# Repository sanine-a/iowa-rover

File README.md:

iowa-rover
==========

hardware & software for the new Iowa Mars rover exhibit.

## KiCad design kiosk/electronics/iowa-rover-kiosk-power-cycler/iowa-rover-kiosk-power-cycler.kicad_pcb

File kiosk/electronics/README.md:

Iowa Science Rover - Electronics
================================

Due to the myriad inputs and outputs that need to be managed, the electronics of the kiosk have been split into
a constellation of connected boards rather than using a single monolithic board. The scheme of connections is
as follows:

[

  * **Arduino Mega**: This is an ATmega2560-based microcontroller, used as the central processor for the kiosk.
  * **Mega Adapter**: This provides a convenient 40-pin ribbon cable connection between the Arduino Mega and the
    main board. It carries power from the main board to the Arduino.
  * **Main Board**: The heart of the kiosk. It carries the comms radio, the 5V regulator to step down from the 12V
    power supply, the ATtiny84 chip to drive the RFID programmer's RFID reader, and connectors to attach all of the
    peripheral boards to the Arduino.
  * **RFID Programmer**: This board carries an ID-12LA RFID reader and a set of buttons. It is used to configure new
    tags appropriately so that they will work with the kiosk, and it is kept inside the kiosk cabinet under normal
    circumstances. It connects to the main board with a 12-pin ribbon cable.
  * **RFID**: These four identical boards are the RFID readers used to read the tags. They each have their own ID-12LA
    reader and an ATtiny84 chip to drive them over the I2C bus. They also carry jumpers that permit setting the I2C bus
    address of each board, allowing them to be daisy-chained. They connect to each other and to the main board with
    4-pin KK connectors.
  * **Lamps**: This board drives the lamps above the RFID readers, the READY, ERROR, and RUNNING lamps, and both the
    lamp and button inside the TRANSMIT button. It is connected to the main board with an 8-pin ribbon cable.
  * **Level Buttons**: This board drives the lamps and buttons below the RFID readers (but not the bar graphs). It is
    connnected to the main board with a 16-pin ribbon cable.
  * **LEDs**: These NeoPixels are the bar graphs, and are chained together with wire-to-wire inline connectors. They
    connect to the main board with a 3-pin KK connector.

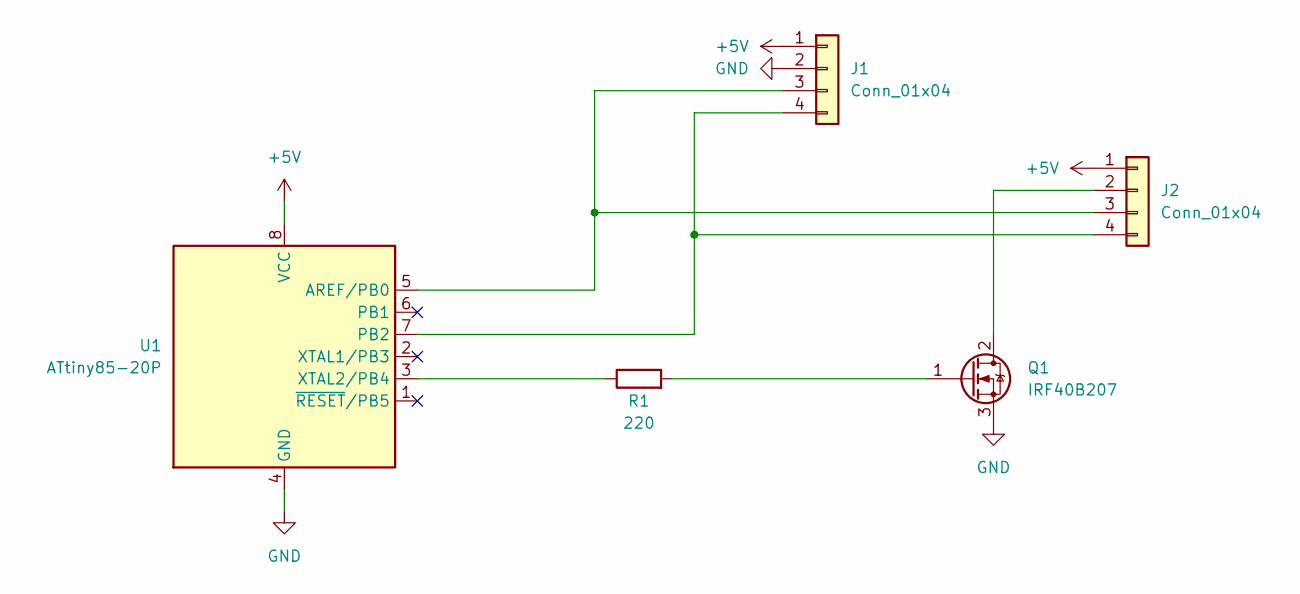
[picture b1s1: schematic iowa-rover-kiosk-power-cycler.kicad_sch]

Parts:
J1, J2: Conn_01x04; Molex_KK-254_AE-6410-04A_1x04_P2.54mm_Vertical
Q1: IRF40B207; TO-220-3_Vertical
R1: 220; R_Axial_DIN0207_L6.3mm_D2.5mm_P7.62mm_Horizontal
U1: ATtiny85-20P; DIP-8_W7.62mm

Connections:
+5V: J1.1, J2.1, U1.8 (VCC)
GND: J1.2, Q1.3 (S), U1.4 (GND)
unnamed: J1.3, J2.3, U1.5 (AREF/PB0)
unnamed: J1.4, J2.4, U1.7 (PB2)
unnamed: J2.2, Q1.2 (D)
unnamed: Q1.1 (G), R1.2
unnamed: R1.1, U1.3 (XTAL2/PB4)

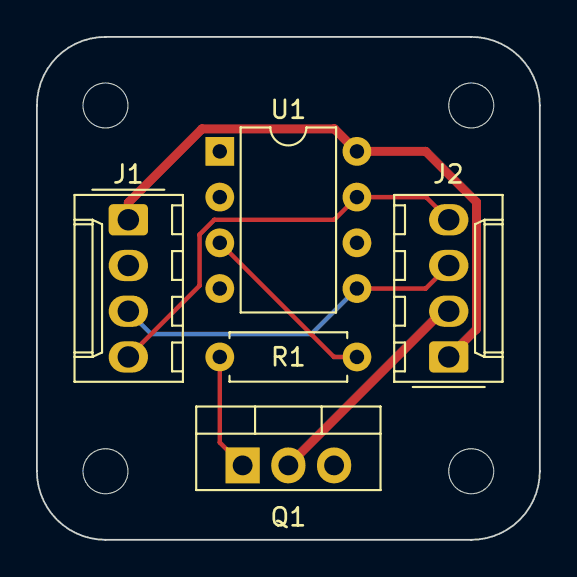
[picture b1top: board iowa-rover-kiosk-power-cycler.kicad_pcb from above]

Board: 2 copper layers, 27.9 x 27.9 mm, 5 parts (0 on the bottom side), 7 nets.

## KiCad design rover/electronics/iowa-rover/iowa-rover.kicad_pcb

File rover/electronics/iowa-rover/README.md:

Iowa Science Rover - Rover Controller
=====================================

The main controller board for the SMM revision of the Iowa Science Rover.

The Metro Mini listens for commands from the kiosk via the radio transceiver, and then executes
the received commands via the motors. The switch allows the controller to choose which kiosk it
listens to, and the trimpot allows maintenance technicians to correct for any directional drift due
to motor wear over time.

Parts
-----

 * [TB6612 Motor Driver](https://www.adafruit.com/product/2448)
 * [RFM69HCW Transceiver](https://www.adafruit.com/product/3070)
 * [Metro Mini v2](https://www.adafruit.com/product/2590)
 * [2k Trimpot](https://www.digikey.com/en/products/detail/bourns-inc/3352T-1-202LF/1088345)
 * [SPDT Switch](https://www.digikey.com/en/products/detail/bourns-inc/3352T-1-202LF/1088345)
 * [USB-C Power Connector](https://www.adafruit.com/product/4907)
 * [Screw Terminals](https://www.digikey.com/en/products/detail/molex/0398800302/2421325)
 * [Motors](https://www.adafruit.com/product/3802)

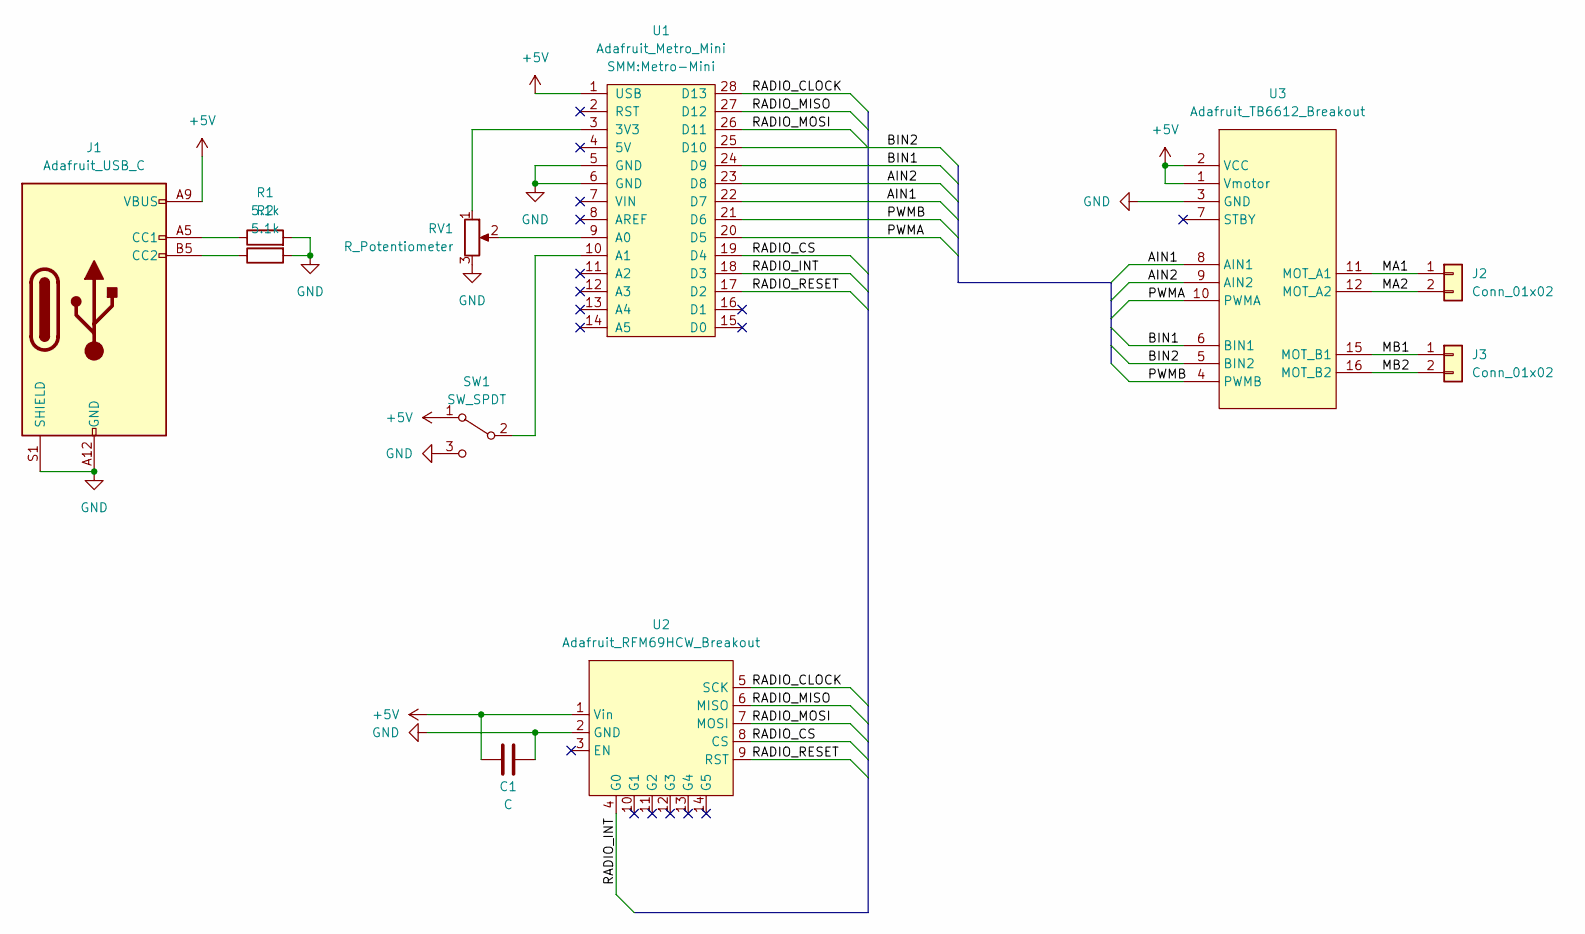
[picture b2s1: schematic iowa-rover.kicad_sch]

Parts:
C1: C; C_Disc_D4.3mm_W1.9mm_P5.00mm
J1: Adafruit_USB_C
J2, J3: Conn_01x02; TerminalBlock-2_P5.08mm_small
R1, R2: 5.1k; Resistor_L6.3mm_D2.5mm_P10.16mm_Horizontal
RV1: R_Potentiometer; Rover_Trimpot
SW1: SW_SPDT; SW_EG1218
U1: Adafruit_Metro_Mini; Metro-Mini
U2: Adafruit_RFM69HCW_Breakout; Adafruit RFM69HCW Breakout
U3: Adafruit_TB6612_Breakout

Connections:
+5V: C1.1, J1.A9 (VBUS), J1.B9 (VBUS), SW1.1 (A), U1.1 (USB), U2.1 (Vin), U3.1 (Vmotor), U3.2 (VCC)
/AIN1: U1.22 (D7), U3.8 (AIN1)
/AIN2: U1.23 (D8), U3.9 (AIN2)
/BIN1: U1.24 (D9), U3.6 (BIN1)
/BIN2: U1.25 (D10), U3.5 (BIN2)
/MA1: J2.1, U3.11 (MOT_A1)
/MA2: J2.2, U3.12 (MOT_A2)
/MB1: J3.1, U3.15 (MOT_B1)
/MB2: J3.2, U3.16 (MOT_B2)
/PWMA: U1.20 (D5), U3.10 (PWMA)
/PWMB: U1.21 (D6), U3.4 (PWMB)
/RADIO_CLOCK: U1.28 (D13), U2.5 (SCK)
/RADIO_CS: U1.19 (D4), U2.8 (CS)
/RADIO_INT: U1.18 (D3), U2.4 (G0)
/RADIO_MISO: U1.27 (D12), U2.6 (MISO)
/RADIO_MOSI: U1.26 (D11), U2.7 (MOSI)
/RADIO_RESET: U1.17 (D2), U2.9 (RST)
GND: C1.2, J1.A12 (GND), J1.B12 (GND), J1.S1 (SHIELD), R1.2, R2.2, RV1.3, SW1.3 (C), U1.5 (GND), U1.6 (GND), U2.2 (GND), U3.3 (GND), U3.13 (GND), U3.14 (GND)
unnamed: J1.A5 (CC1), R1.1
unnamed: J1.B5 (CC2), R2.1
unnamed: SW1.2 (B), U1.10 (A1)
unnamed: RV1.1, U1.3 (3V3)
unnamed: RV1.2, U1.9 (A0)

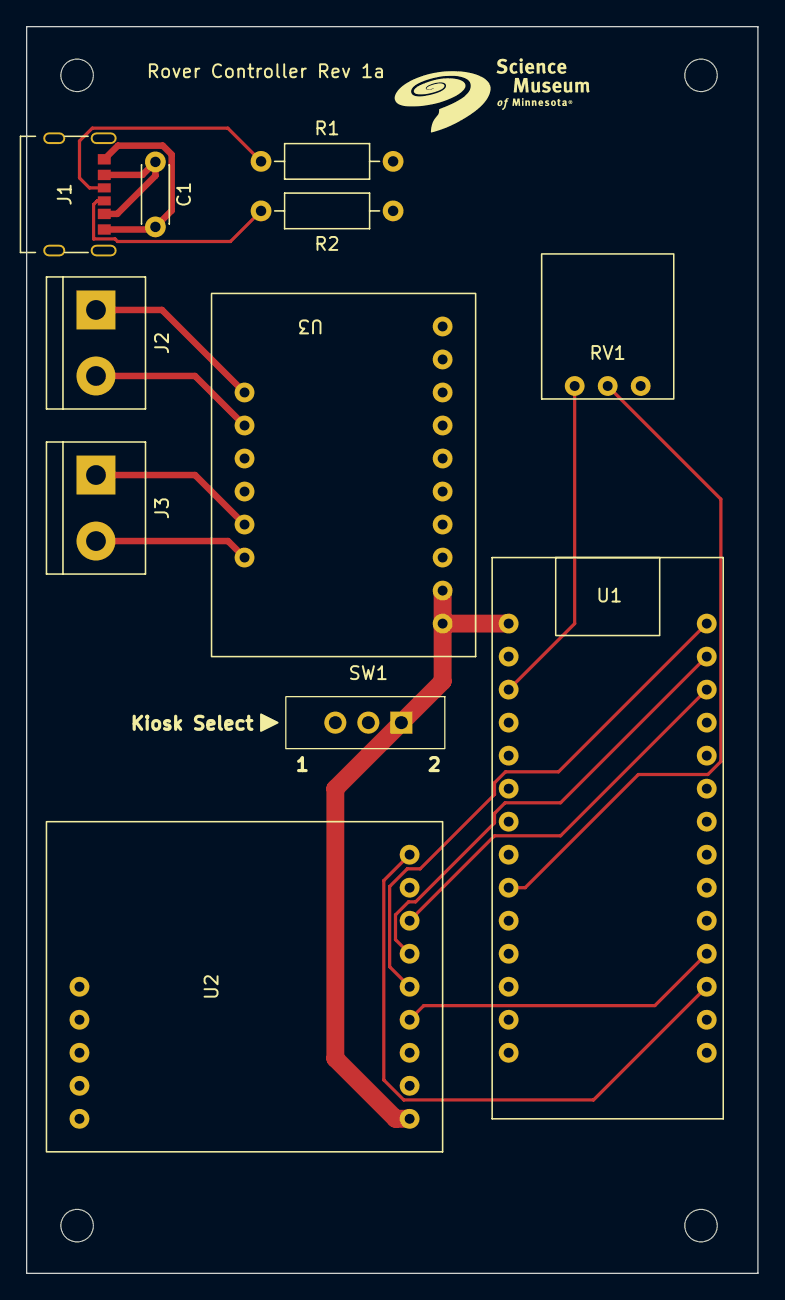
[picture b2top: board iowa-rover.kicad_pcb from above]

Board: 4 copper layers, 56.3 x 95.9 mm, 11 parts (0 on the bottom side), 23 nets.

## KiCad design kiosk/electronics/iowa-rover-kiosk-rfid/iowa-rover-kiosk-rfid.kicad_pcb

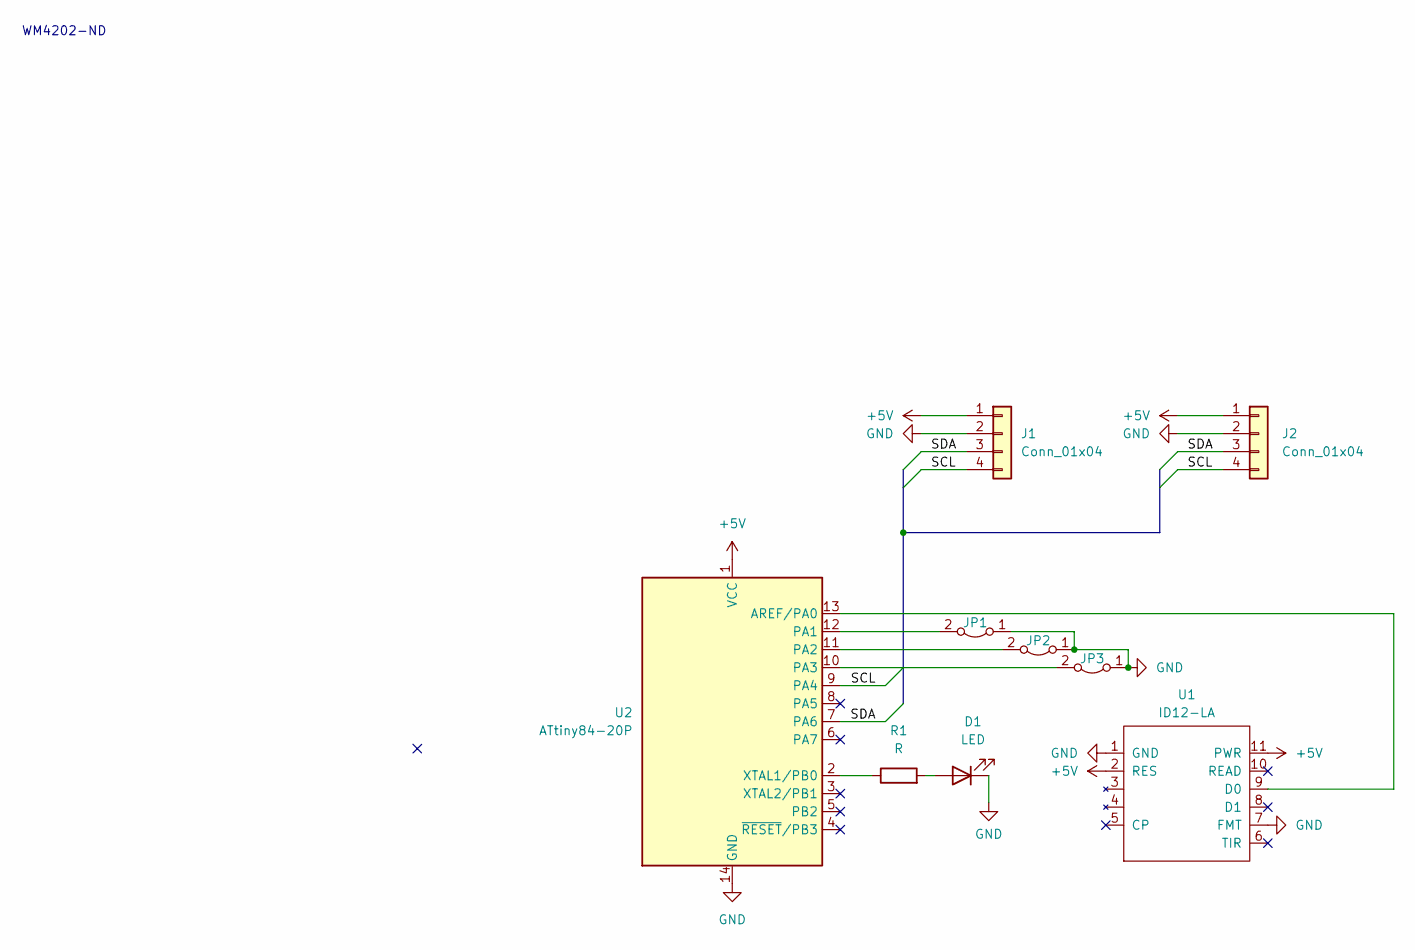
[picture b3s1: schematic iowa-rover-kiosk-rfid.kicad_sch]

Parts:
D1: LED; LED_D3.0mm
J1, J2: Conn_01x04; KK-1x04
JP1, JP2, JP3: Jumper_2_Bridged; SolderJumper-2_P1.3mm_Bridged_RoundedPad1.0x1.5mm
R1: R; Resistor_L6.3mm_D2.5mm_P10.16mm_Horizontal
U1: ID12-LA; ID-12LA-Inverted
U2: ATtiny84-20P; DIP-14_W7.62mm

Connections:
+5V: J1.1, J2.1, U1.2 (RES), U1.11 (PWR), U2.1 (VCC)
/SCL: J1.4, J2.4, U2.9 (PA4)
/SDA: J1.3, J2.3, U2.7 (PA6)
GND: D1.1 (K), J1.2, J2.2, JP1.1 (A), JP2.1 (A), JP3.1 (A), U1.1 (GND), U1.7 (FMT), U2.14 (GND)
unnamed: D1.2 (A), R1.2
unnamed: JP1.2 (B), U2.12 (PA1)
unnamed: JP2.2 (B), U2.11 (PA2)
unnamed: JP3.2 (B), U2.10 (PA3)
unnamed: U1.9 (D0), U2.13 (AREF/PA0)
unnamed: R1.1, U2.2 (XTAL1/PB0)

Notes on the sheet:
WM4202-ND

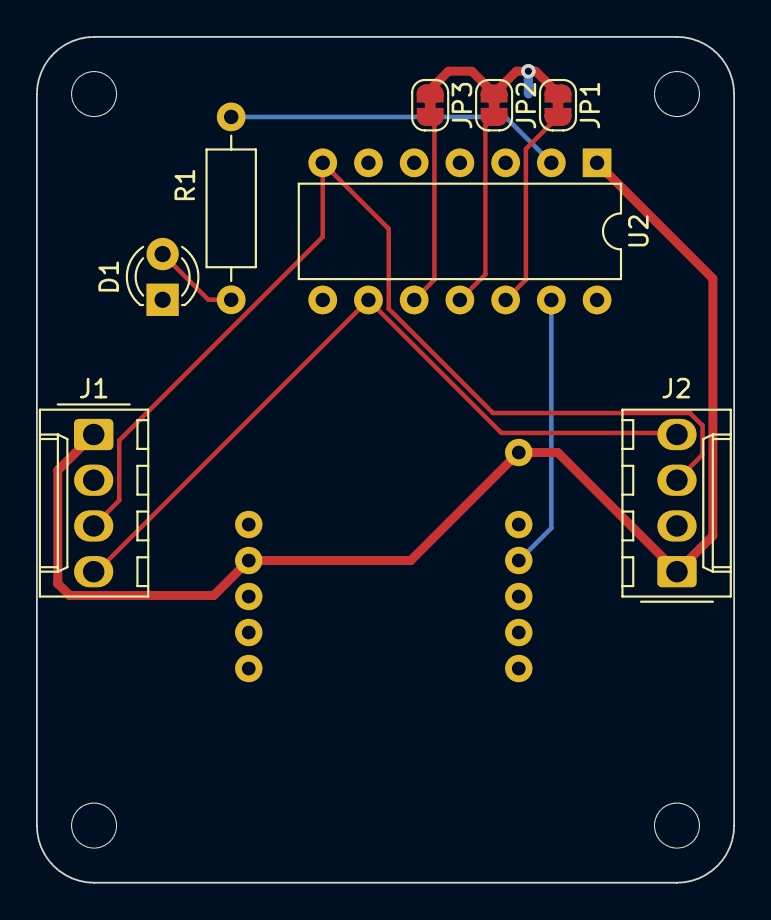
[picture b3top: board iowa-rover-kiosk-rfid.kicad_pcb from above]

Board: 2 copper layers, 38.7 x 47.0 mm, 9 parts (0 on the bottom side), 10 nets.

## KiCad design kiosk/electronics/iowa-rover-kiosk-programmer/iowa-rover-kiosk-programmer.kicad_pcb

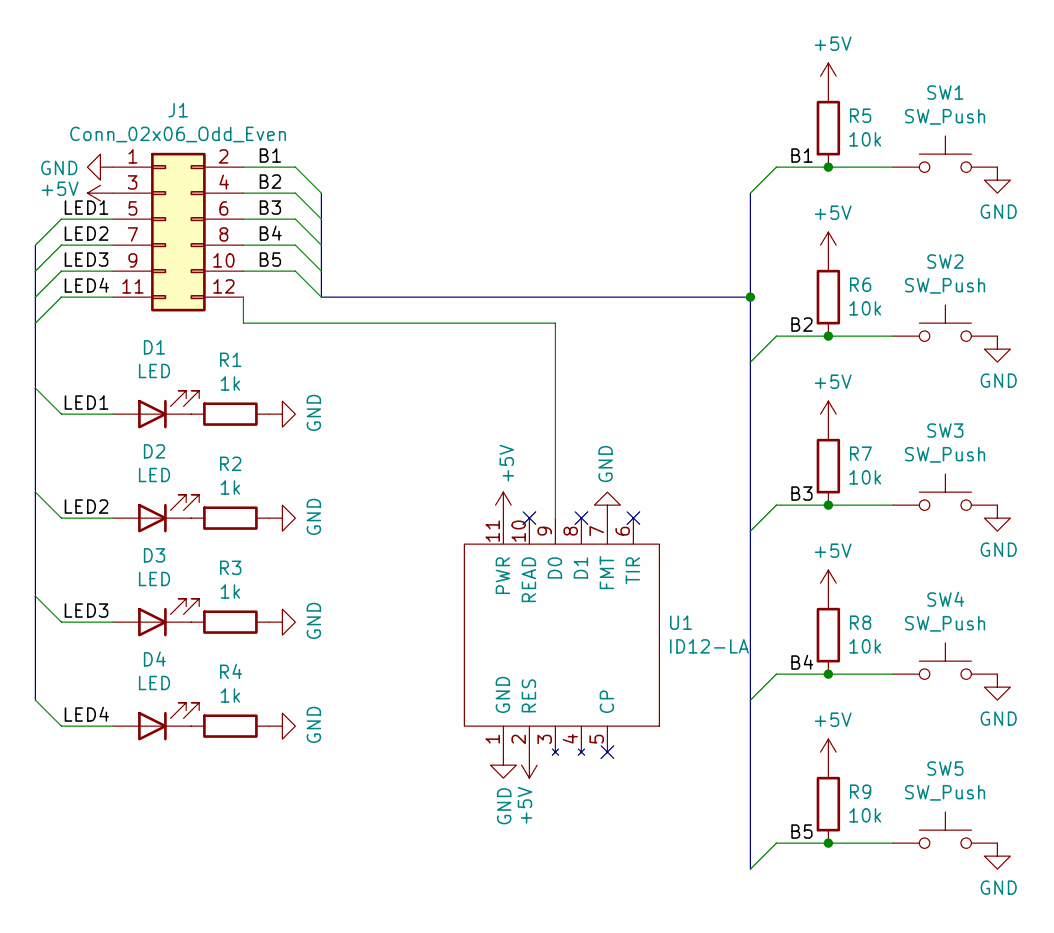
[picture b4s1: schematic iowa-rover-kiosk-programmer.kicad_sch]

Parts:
D1, D2, D3, D4: LED; LED_D3.0mm
J1: Conn_02x06_Odd_Even; PinHeader_2x06_P2.54mm_Vertical
R1, R2, R3, R4: 1k; R_Axial_DIN0207_L6.3mm_D2.5mm_P10.16mm_Horizontal
R5, R6, R7, R8, R9: 10k; R_Axial_DIN0207_L6.3mm_D2.5mm_P10.16mm_Horizontal
SW1, SW2, SW3, SW4, SW5: SW_Push; SW_PUSH_6mm_H4.3mm
U1: ID12-LA; ID-12LA

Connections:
+5V: J1.3, R5.1, R6.1, R7.1, R8.1, R9.1, U1.2 (RES), U1.11 (PWR)
/B1: J1.2, R5.2, SW1.1
/B2: J1.4, R6.2, SW2.1
/B3: J1.6, R7.2, SW3.1
/B4: J1.8, R8.2, SW4.1
/B5: J1.10, R9.2, SW5.1
/LED1: D1.2 (A), J1.5
/LED2: D2.2 (A), J1.7
/LED3: D3.2 (A), J1.9
/LED4: D4.2 (A), J1.11
GND: J1.1, R1.1, R2.1, R3.1, R4.1, SW1.2, SW2.2, SW3.2, SW4.2, SW5.2, U1.1 (GND), U1.7 (FMT)
unnamed: D1.1 (K), R1.2
unnamed: D2.1 (K), R2.2
unnamed: D3.1 (K), R3.2
unnamed: D4.1 (K), R4.2
unnamed: J1.12, U1.9 (D0)

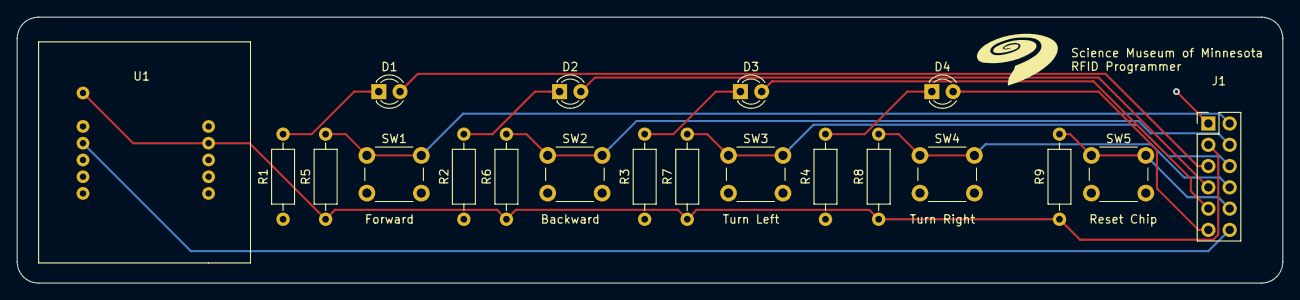
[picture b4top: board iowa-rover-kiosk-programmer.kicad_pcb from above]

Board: 2 copper layers, 151.1 x 31.8 mm, 20 parts (0 on the bottom side), 16 nets.

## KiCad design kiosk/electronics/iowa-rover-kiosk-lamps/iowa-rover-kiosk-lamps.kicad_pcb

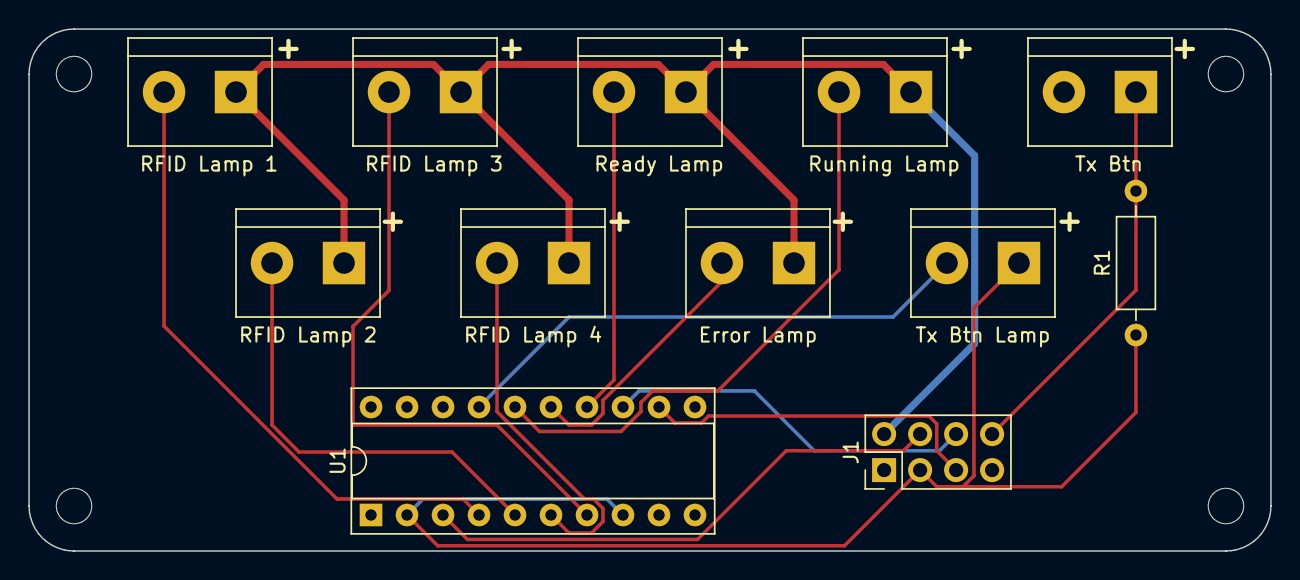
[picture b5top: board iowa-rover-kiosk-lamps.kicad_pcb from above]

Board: 2 copper layers, 87.6 x 36.8 mm, 12 parts (0 on the bottom side), 15 nets.

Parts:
Error Lamp: Lamp; TerminalBlock-2_P5.08mm_small
J1: Conn_01x08; PinHeader_2x04_P2.54mm_Vertical
R1: R; Resistor_L6.3mm_D2.5mm_P10.16mm_Horizontal
RFID Lamp 1, RFID Lamp 2, RFID Lamp 3, RFID Lamp 4: Lamp; TerminalBlock-2_P5.08mm_small
Ready Lamp: Lamp; TerminalBlock-2_P5.08mm_small
Running Lamp: Lamp; TerminalBlock-2_P5.08mm_small
Tx Btn: SW_Push; TerminalBlock-2_P5.08mm_small
Tx Btn Lamp: Lamp; TerminalBlock-2_P5.08mm_small
U1: TPIC6B595; DIP-20_W7.62mm_Socket

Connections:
+5V: J1.3, R1.1, Tx Btn Lamp.1 (-), U1.2 (VCC), U1.8 (SRCLR)
+12V: Error Lamp.1 (-), J1.2, RFID Lamp 1.1 (-), RFID Lamp 2.1 (-), RFID Lamp 3.1 (-), RFID Lamp 4.1 (-), Ready Lamp.1 (-), Running Lamp.1 (-)
GND: J1.1, Tx Btn.2, U1.9 (G), U1.10 (GND), U1.11 (GND), U1.19 (GND)
unnamed: J1.4, U1.3 (SERIN)
unnamed: J1.5, U1.12 (RCK)
unnamed: J1.6, U1.13 (SRCK)
unnamed: J1.8, R1.2, Tx Btn.1
unnamed: RFID Lamp 1.2 (+), U1.4 (DRAIN0)
unnamed: RFID Lamp 2.2 (+), U1.5 (DRAIN1)
unnamed: RFID Lamp 3.2 (+), U1.7 (DRAIN3)
unnamed: RFID Lamp 4.2 (+), U1.6 (DRAIN2)
unnamed: Ready Lamp.2 (+), U1.14 (DRAIN4)
unnamed: Error Lamp.2 (+), U1.15 (DRAIN5)
unnamed: Running Lamp.2 (+), U1.16 (DRAIN6)
unnamed: Tx Btn Lamp.2 (+), U1.17 (DRAIN7)

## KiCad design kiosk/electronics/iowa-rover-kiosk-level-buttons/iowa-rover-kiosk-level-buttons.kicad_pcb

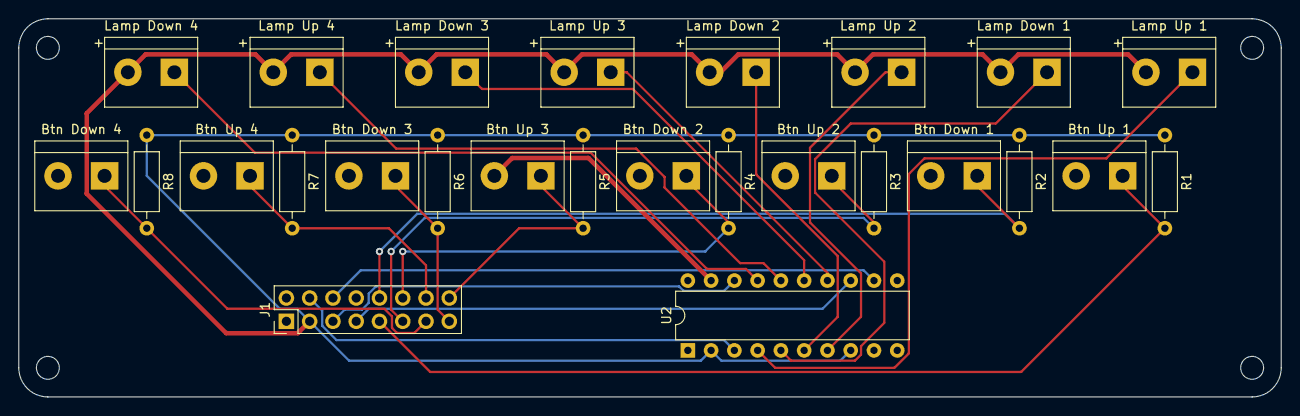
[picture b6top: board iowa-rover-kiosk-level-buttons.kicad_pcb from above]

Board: 2 copper layers, 137.8 x 41.3 mm, 26 parts (0 on the bottom side), 22 nets.

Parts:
Btn Down 1, Btn Down 2, Btn Down 3, Btn Down 4: SW_Push; TerminalBlock-2_P5.08mm_small
Btn Up 1, Btn Up 2, Btn Up 3, Btn Up 4: SW_Push; TerminalBlock-2_P5.08mm_small
J1: Conn_02x08_Top_Bottom; PinHeader_2x08_P2.54mm_Vertical
Lamp Down 1, Lamp Down 2, Lamp Down 3, Lamp Down 4: Lamp; TerminalBlock-2_P5.08mm_small
Lamp Up 1, Lamp Up 2, Lamp Up 3, Lamp Up 4: Lamp; TerminalBlock-2_P5.08mm_small
R1, R2, R3, R4, R5, R6, R7, R8: R; Resistor_L6.3mm_D2.5mm_P10.16mm_Horizontal
U2: TPIC6B595; DIP-20_W7.62mm

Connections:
+5V: J1.3, Lamp Down 1.2 (+), Lamp Down 2.2 (+), Lamp Down 3.2 (+), Lamp Down 4.2 (+), Lamp Up 1.2 (+), Lamp Up 2.2 (+), Lamp Up 3.2 (+), Lamp Up 4.2 (+), R1.1, R2.1, R3.1, R4.1, R5.1, R6.1, R7.1, R8.1, U2.2 (VCC), U2.8 (SRCLR)
/CIPO: J1.5, U2.18 (SEROUT)
/CLOCK: J1.7, U2.13 (SRCK)
/COPI: J1.4, U2.3 (SERIN)
/LATCH: J1.6, U2.12 (RCK)
GND: Btn Down 1.2, Btn Down 2.2, Btn Down 3.2, Btn Down 4.2, Btn Up 1.2, Btn Up 2.2, Btn Up 3.2, Btn Up 4.2, J1.1, U2.9 (G), U2.10 (GND), U2.11 (GND), U2.19 (GND)
unnamed: Btn Up 1.1, J1.9, R1.2
unnamed: Btn Down 1.1, J1.10, R2.2
unnamed: Btn Up 2.1, J1.11, R3.2
unnamed: Btn Down 2.1, J1.12, R4.2
unnamed: Btn Down 4.1, J1.13, R8.2
unnamed: Btn Up 4.1, J1.14, R7.2
unnamed: Btn Down 3.1, J1.15, R6.2
unnamed: Btn Up 3.1, J1.16, R5.2
unnamed: Lamp Up 1.1 (-), U2.4 (DRAIN0)
unnamed: Lamp Down 1.1 (-), U2.5 (DRAIN1)
unnamed: Lamp Up 2.1 (-), U2.7 (DRAIN3)
unnamed: Lamp Down 2.1 (-), U2.6 (DRAIN2)
unnamed: Lamp Up 3.1 (-), U2.14 (DRAIN4)
unnamed: Lamp Down 3.1 (-), U2.15 (DRAIN5)
unnamed: Lamp Up 4.1 (-), U2.16 (DRAIN6)
unnamed: Lamp Down 4.1 (-), U2.17 (DRAIN7)

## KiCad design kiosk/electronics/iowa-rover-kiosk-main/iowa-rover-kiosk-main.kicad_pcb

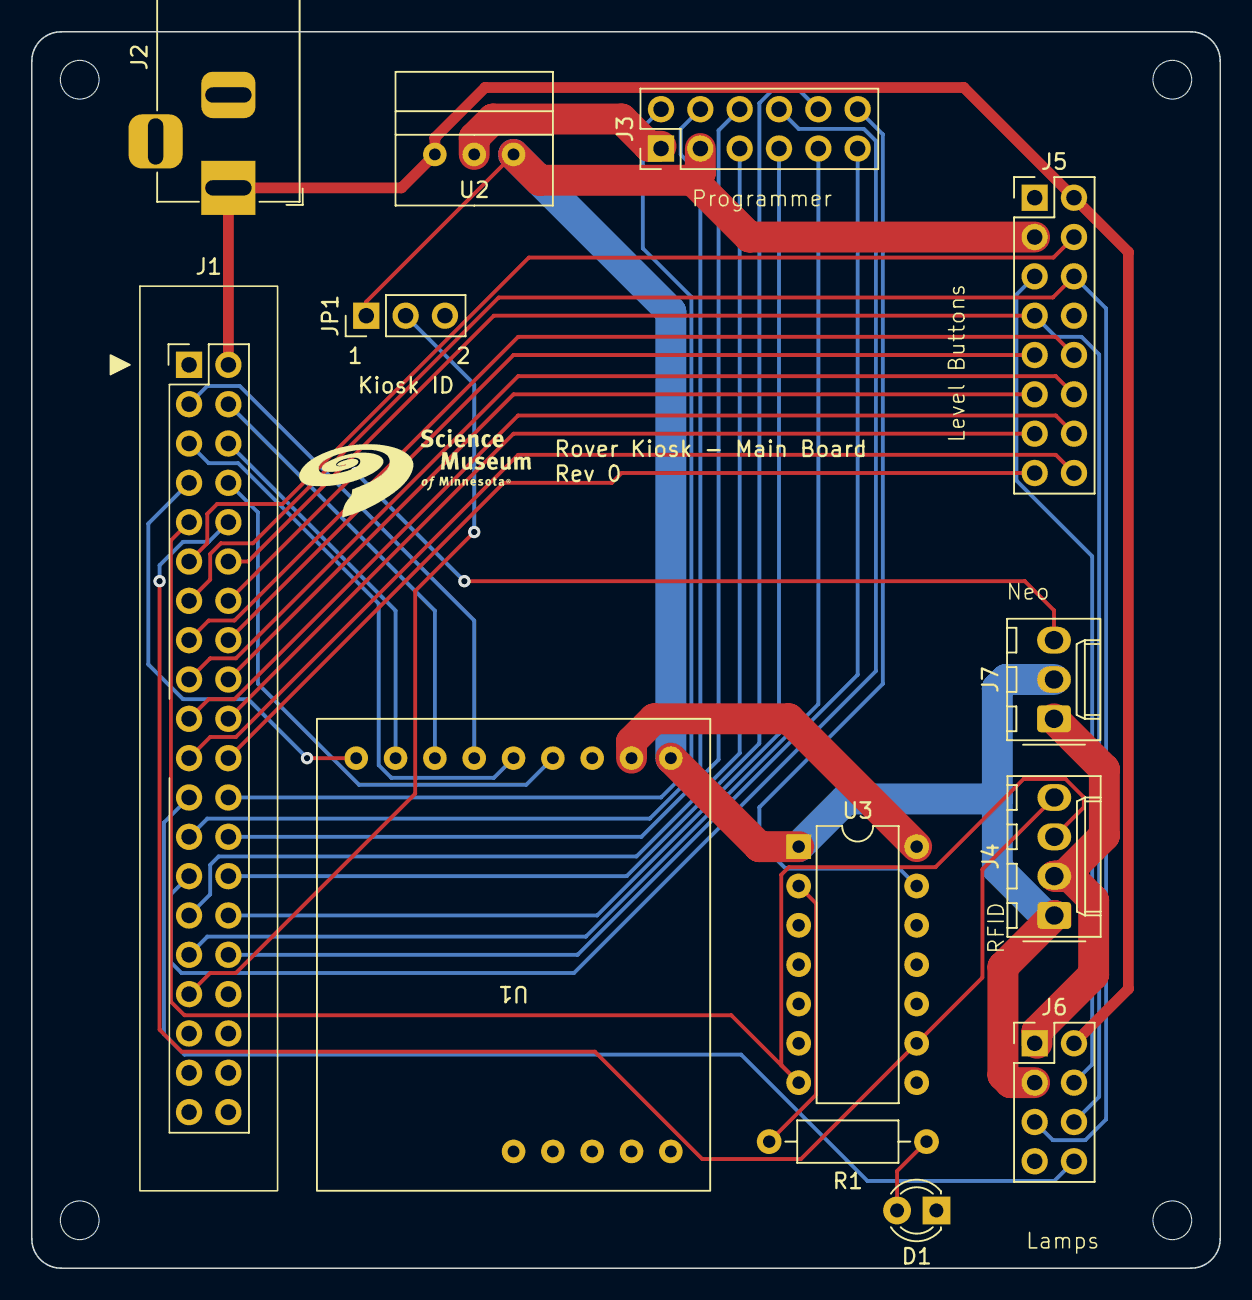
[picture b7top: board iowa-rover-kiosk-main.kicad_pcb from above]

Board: 2 copper layers, 76.8 x 79.9 mm, 13 parts (0 on the bottom side), 38 nets.

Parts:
D1: LED; LED_D3.0mm
J1: PinHeader_2x20_Ribbon
J2: Barrel_Jack; BarrelJack_Horizontal
J3: Conn_02x06_Odd_Even; PinHeader_2x06_P2.54mm_Vertical
J4: Conn_01x04; Molex_KK-254_AE-6410-04A_1x04_P2.54mm_Vertical
J5: Conn_02x08_Top_Bottom; PinHeader_2x08_P2.54mm_Vertical
J6: Conn_01x08; PinHeader_2x04_P2.54mm_Vertical
J7: Conn_01x03; Molex_KK-254_AE-6410-03A_1x03_P2.54mm_Vertical
JP1: Jumper_3_Open; PinHeader_1x03_P2.54mm_Vertical
R1: R; Resistor_L6.3mm_D2.5mm_P10.16mm_Horizontal
U1: Adafruit_RFM69HCW_Breakout; Adafruit RFM69HCW Breakout
U2: I50115
U3: ATtiny84-20P; DIP-14_W7.62mm

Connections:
+5V: J3.3, J4.1, J5.3, J6.3, J7.2, JP1.1 (A), U1.1 (Vin), U2.3 (+5V), U3.1 (VCC)
+12V: J1.2 (VIN), J2.1, J5.2, J6.2, U2.1 (PWR)
/B1: J1.24 (BP1), J3.2
/B1_DOWN: J1.15 (B1_DOWN), J5.10
/B1_UP: J1.16 (B1_UP), J5.9
/B2: J1.25 (BP2), J3.4
/B2_DOWN: J1.17 (B2_DOWN), J5.12
/B2_UP: J1.18 (B2_UP), J5.11
/B3: J1.26 (BP3), J3.6
/B3_DOWN: J1.19 (B3_DOWN), J5.14
/B3_UP: J1.20 (B3_UP), J5.13
/B4: J1.27 (BP4), J3.8
/B4_DOWN: J1.21 (B4_DOWN), J5.16
/B4_UP: J1.22 (B4_UP), J5.15
/B5: J1.28 (BP5), J3.10
/BTX: J1.23 (BTX), J6.8
/CLOCK: J1.12 (D10_CLOCK), J5.7, J6.6
/DATA: J1.11 (D12_DATA), J5.4
/LATCH: J1.13 (D9_LATCH), J5.6, J6.5
/LED1: J1.29 (LP1), J3.5
/LED2: J1.30 (LP2), J3.7
/LED3: J1.31 (LP3), J3.9
/LED4: J1.32 (LP4), J3.11
/SCL: J1.10 (D21_SCL), J4.4, U3.9 (PA4)
/SDA: J1.9 (D20_SDA), J4.3, U3.7 (PA6)
GND: D1.1 (K), J1.1 (GND), J2.2, J3.1, J4.2, J5.1, J6.1, J7.1, JP1.3 (B), U1.2 (GND), U2.2 (GND), U3.14 (GND)
unnamed: D1.2 (A), R1.2
unnamed: J1.14 (D6_NEO), J7.3
unnamed: J1.8 (D19_INT), U1.4 (G0)
unnamed: J1.7 (D45_RST), U1.9 (RST)
unnamed: J1.3 (D50_CIPO), U1.6 (MISO)
unnamed: J1.4 (D51_COPI), U1.7 (MOSI)
unnamed: J1.5 (D52_SCK), U1.5 (SCK)
unnamed: J1.6 (D53_CS), U1.8 (CS)
unnamed: J1.33 (KIOSK), JP1.2 (C)
unnamed: J3.12, U3.13 (AREF/PA0)
unnamed: J5.5, J6.4
unnamed: R1.1, U3.2 (XTAL1/PB0)

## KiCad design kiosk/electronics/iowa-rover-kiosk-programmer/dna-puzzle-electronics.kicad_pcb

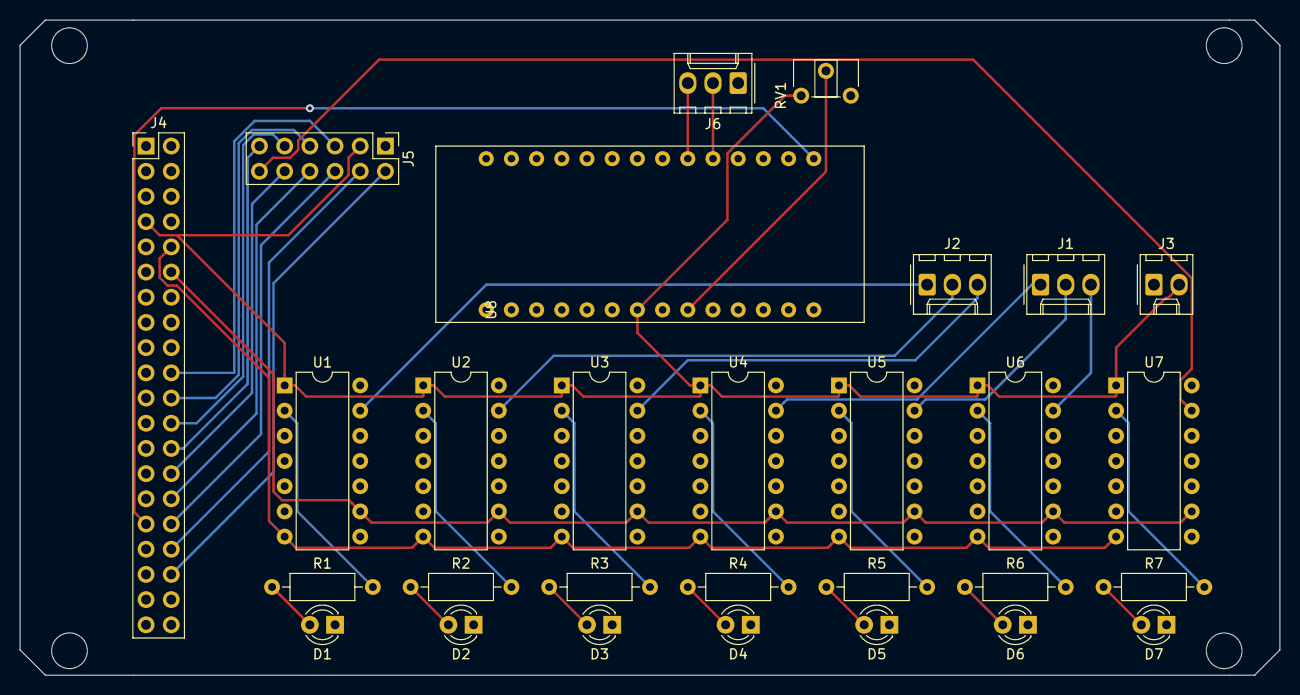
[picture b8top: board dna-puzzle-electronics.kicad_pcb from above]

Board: 2 copper layers, 127.0 x 66.0 mm, 29 parts (0 on the bottom side), 38 nets.

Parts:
D1, D2, D3, D4, D5, D6, D7: LED; LED_D3.0mm
J1, J2, J6: Conn_01x03; Molex_KK-254_AE-6410-03A_1x03_P2.54mm_Vertical
J3: Conn_01x02; Molex_KK-254_AE-6410-02A_1x02_P2.54mm_Vertical
J4: SMM_Mega_Shield_Connector; PinHeader_2x20_P2.54mm_Vertical
J5: Conn_02x06_Odd_Even; PinHeader_2x06_P2.54mm_Vertical
R1, R2, R3, R4, R5, R6, R7: R; R_Axial_DIN0207_L6.3mm_D2.5mm_P10.16mm_Horizontal
RV1: R_POT; Potentiometer_ACP_CA6-H2,5_Horizontal
U1, U2, U3, U4, U5, U6, U7: ATtiny84-20PU; DIP-14_W7.62mm
U8: Adafruit_Metro_Mini; Metro-Mini

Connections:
+5V: J3.2, J4.7, J5.3, RV1.1, U1.1, U2.1, U3.1, U4.1, U5.1, U6.1, U7.1, U8.7
/RFID1: J2.1, U1.13
/RFID2: J2.2, U2.13
/RFID3: J2.3, U3.13
/RFID4: J1.1, U4.13
/RFID5: J1.2, U5.13
/RFID6: J1.3, U6.13
/SCL: J4.10, U1.7, U2.7, U3.7, U4.7, U5.7, U6.7, U7.7
/SDA: J4.12, U1.9, U2.9, U3.9, U4.9, U5.9, U6.9, U7.9
GND: D1.1, D2.1, D3.1, D4.1, D5.1, D6.1, D7.1, J3.1, J4.1, J5.1, J6.1, RV1.3, U1.14, U2.14, U3.14, U4.14, U5.14, U6.14, U7.14, U8.5
unnamed: D1.2, R1.1
unnamed: D2.2, R2.1
unnamed: D3.2, R3.1
unnamed: D4.2, R4.1
unnamed: D5.2, R5.1
unnamed: D6.2, R6.1
unnamed: D7.2, R7.1
unnamed: J4.20, J5.5
unnamed: J4.22, J5.7
unnamed: J4.24, J5.9
unnamed: J4.26, J5.11
unnamed: J4.28, J5.10
unnamed: J4.30, J5.8
unnamed: J4.31, U8.15
unnamed: J4.32, J5.6
unnamed: J4.34, J5.4
unnamed: J4.36, J5.2
unnamed: J5.12, U7.13
unnamed: J6.2, U8.19
unnamed: J6.3, U8.20
unnamed: R1.2, U1.2
unnamed: R2.2, U2.2
unnamed: R3.2, U3.2
unnamed: R4.2, U4.2
unnamed: R5.2, U5.2
unnamed: R6.2, U6.2
unnamed: R7.2, U7.2
unnamed: RV1.2, U8.9

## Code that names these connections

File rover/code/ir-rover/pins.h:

#pragma once

// radio module
#define RADIO_CS 4
#define RADIO_INT 3
#define RADIO_RST 2

// h-bridge
#define AIN1 7
#define AIN2 8
#define PWMA 5

#define BIN1 9
#define BIN2 10
#define PWMB 6

// configuration peripherals
#define TRIMPOT A0
#define KIOSK_SELECT A1

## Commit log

2023-09-21 draw board
2023-09-21 generate gerbers
2023-09-21 add kiosk level buttons board
2023-09-26 initial pass at board drawings
2023-09-27 add eeprom code
2023-09-27 add scheduler
2023-09-28 fix sda/scl bus connections
2023-10-03 add gerbers and initial radio code
2023-10-03 fix bug with radio buffer length
2023-10-03 set up simple radio console
2023-10-04 update radio power and add electronics PDF and readme
2023-10-04 remove schematics folder
2023-10-04 add kiosk/electronics/README.md
2023-10-05 update board descriptions
2023-10-05 add pdf schematics
2023-10-11 add RFID sketch
2023-10-12 begin writing eeprom hash table
2023-10-16 add unit test skeleton
2023-10-16 begin writing tested HashSlot
2023-10-16 add getters & setters for category and occupied/deleted bits
2023-10-16 implement hash table
2023-10-17 implement programmer leds
2023-10-18 implement basic observer pattern
2023-10-18 fix scheduler lambda usage and add programmer buttons
2023-10-23 add programmer/controller.h
2023-10-24 refactor: flat hierarchy to permit splitting into cpp files
2023-10-24 add skeleton shift register lamps code
2023-10-24 implement rfid readers as signal publishers
2023-10-24 implement rfid programming
2023-10-25 implement basic rfid read/command update/button lighting
2023-10-25 implement bar graphs and increment/decrement
2023-10-25 add skeleton transmitter code
2023-10-26 implement working rover control
2023-10-26 add power cycler for tag removal detection
2023-10-31 fix pin mapping
2023-10-31 add periodic rfid polling
2023-10-31 implement rfid polling
2023-11-01 implement transmit/ready lamp behavior and fix empty slot bug
2023-11-06 use more efficient command encoding
2023-11-06 implement improved command format for kiosk
2023-11-08 add comments and README.md to ir-rover
2023-11-08 remove superfluous sketches and add README.md to kiosk/code
2023-11-08 add README.md
2023-11-08 begin adding comments
2023-11-08 remove superfluous Rfid/* files
2023-11-08 add more comments
2023-11-09 add better comments to shift lamps and transmit
2023-11-10 update README.md and add comments
2023-12-20 implement watchdog timer
2023-12-21 add power cycler kiosk pdf
2024-06-13 add motor ramping
